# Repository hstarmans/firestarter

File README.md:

# Hexastorm PCB

KiCad design files for **Hexastorm**, an open-hardware laser direct imager (LDI). An ESP32-S3 handles communication and motion control, while an iCE40 UP5K FPGA generates synchronized laser pulses for the rotating polygon prism.

The design files are organized into two parts:

## 1. Laser Module

PCBs forming the scanhead assembly (see [hexastorm_design](https://github.com/hstarmans/hexastorm_design) for complete CAD):

* **Prism Drive:** PCBs to spin the optical prism using either an external BLDC motor or an experimental PCB stator motor.
* **Laser Control:** Diode driver and photodiode sync circuit.
* **Maxwell Dock:** Receiver PCB with kinematic ball mounts and magnet sockets.

## 2. Base Board

Single-board controller for 3-axis motion and laser timing. Intended for desktop CNC frames (such as the CNC 3018 Pro, for which it is a drop-in replacement):

* **MCU:** ESP32-S3 (N32R8V) with 8MB Octal PSRAM for line buffers.
* **FPGA:** Lattice iCE40 UP5K for laser pulse timing synced to the prism photodiode index.
* **Camera:** 24-pin FPC connector for an OV2640 camera module.
* **Motion:** Sockets for 3x stepper drivers (TMC2209) for X, Y, and Z axes.
* **Laser:** Header for one laser scanhead.
* **Power:** 24V input with onboard 12V buck regulator for the laser module and cooling fan.
* **USB:** USB-C for data and flashing.

---

# Resources & Links

* **Blog & Build Logs:** [Hackaday.io project](https://hackaday.io/project/21933-open-hardware-fast-high-resolution-laser)
* **BOM & Costing:** Generated with [KiCost](https://github.com/hildogjr/KiCost) (see [developer.md](developer.md))
* **CAD Files:** [hexastorm_design](https://github.com/hstarmans/hexastorm_design)
* **Optical Simulation:** [opticaldesign](https://github.com/hstarmans/opticaldesign)

# Status

* **Exposure Verification:** High-resolution optical scanning and exposure have been validated in hardware (see [demonstration video](https://youtu.be/dR09Tev0cPk)).
* **Base Board:** Fabricated, tested, and verified functional (ESP32-S3, iCE40 UP5K FPGA, stepper drivers, and power regulation).
* **Laser Module:** Scanhead structure, optics, diode driver, and kinematic docking are verified. The integrated PCB stator motor concept is proven, though the latest stator board revision has not yet been tested.

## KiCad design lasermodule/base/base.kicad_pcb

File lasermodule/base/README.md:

# Scanhead Base Plate

Structural bottom floor of the laser scanhead module. Hosts mounting holes for the prism motor assembly, internal optics brackets, and kinematic docking interfaces.
A female pinheader is shown but this one is normally not placed.

## Key Details

* **Role:** Bottom structural plate of scanhead housing
* **Material:** 1.6mm FR4 PCB material
* **Features:** Prism spindle mounting, beam pass-through cutouts, interlocking tabs

---

*Part of the [Hexastorm (Firestarter)](../../README.md) open-hardware laser direct imaging project.*

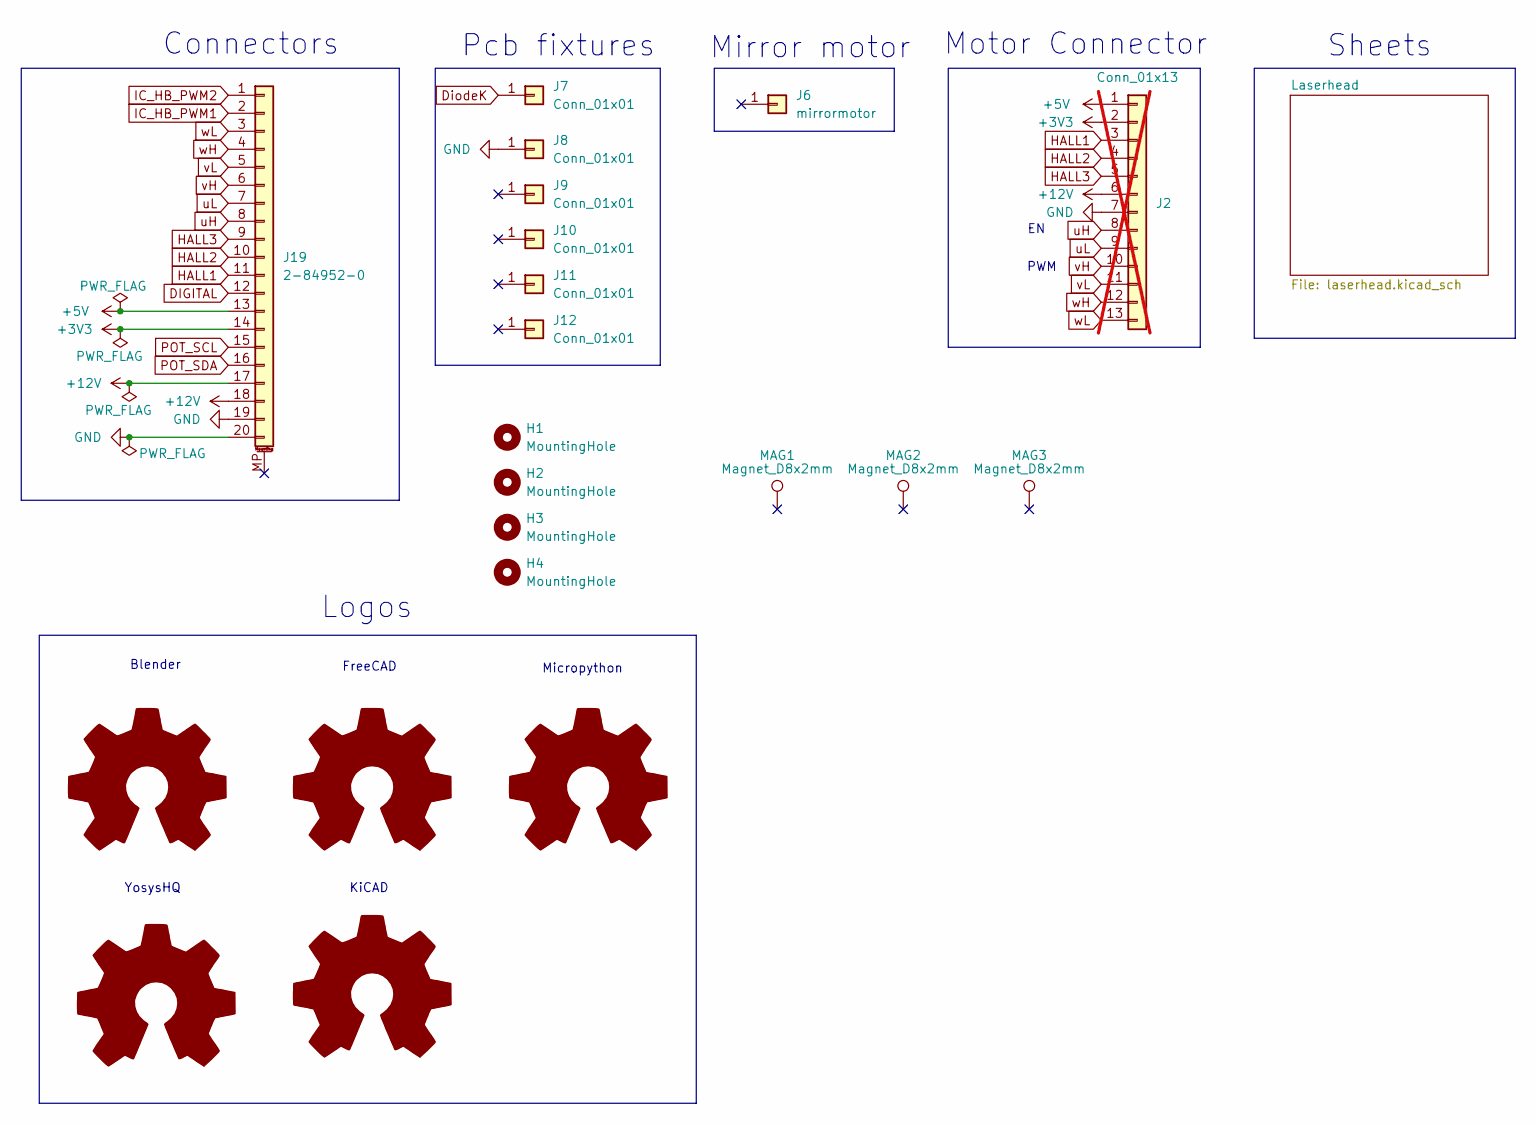
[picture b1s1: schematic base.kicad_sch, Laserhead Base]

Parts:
H1, H2, H3, H4: MountingHole; MountingHole_2.2mm_M2; mouser# 710-970050244
J2: Conn_01x13; PinSocket_1x13_P2.00mm_Vertical; not fitted
J6: mirrormotor; mirror_motor
J7, J8, J9, J10, J11, J12: Conn_01x01; throughholeplate
J19: 2-84952-0; mouser# 571-2-84952-0
L1: Logo_Open_Hardware_Large; blender
L2: Logo_Open_Hardware_Large; yosys
L3: Logo_Open_Hardware_Large; kicad
L4: Logo_Open_Hardware_Large; freecad
L5: Logo_Open_Hardware_Large; micropython
MAG1, MAG2, MAG3: Magnet_D8x2mm; TestPoint_Pad_D8.0mm

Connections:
+3V3: J2.2, J19.14
+5V: J2.1, J19.13; also elsewhere on the board
+12V: J2.6, J19.17, J19.18; also elsewhere on the board
DIGITAL: J19.12; also elsewhere on the board
DiodeK: J7.1 (Pin_1_1); also elsewhere on the board
GND: J2.7, J8.1 (Pin_1_1), J19.19, J19.20; also elsewhere on the board
HALL1: J2.3, J19.11
HALL2: J2.4, J19.10
HALL3: J2.5, J19.9
IC_HB_PWM1: J19.2; also elsewhere on the board
IC_HB_PWM2: J19.1; also elsewhere on the board
POT_SCL: J19.15; also elsewhere on the board
POT_SDA: J19.16; also elsewhere on the board
uH: J2.8, J19.8
uL: J2.9, J19.7
vH: J2.10, J19.6
vL: J2.11, J19.5
wH: J2.12, J19.4
wL: J2.13, J19.3

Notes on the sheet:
PWM
Micropython
YosysHQ
FreeCAD
Logos
KiCAD
Motor Connector
Blender
Connectors
Sheets
Mirror motor
Pcb fixtures

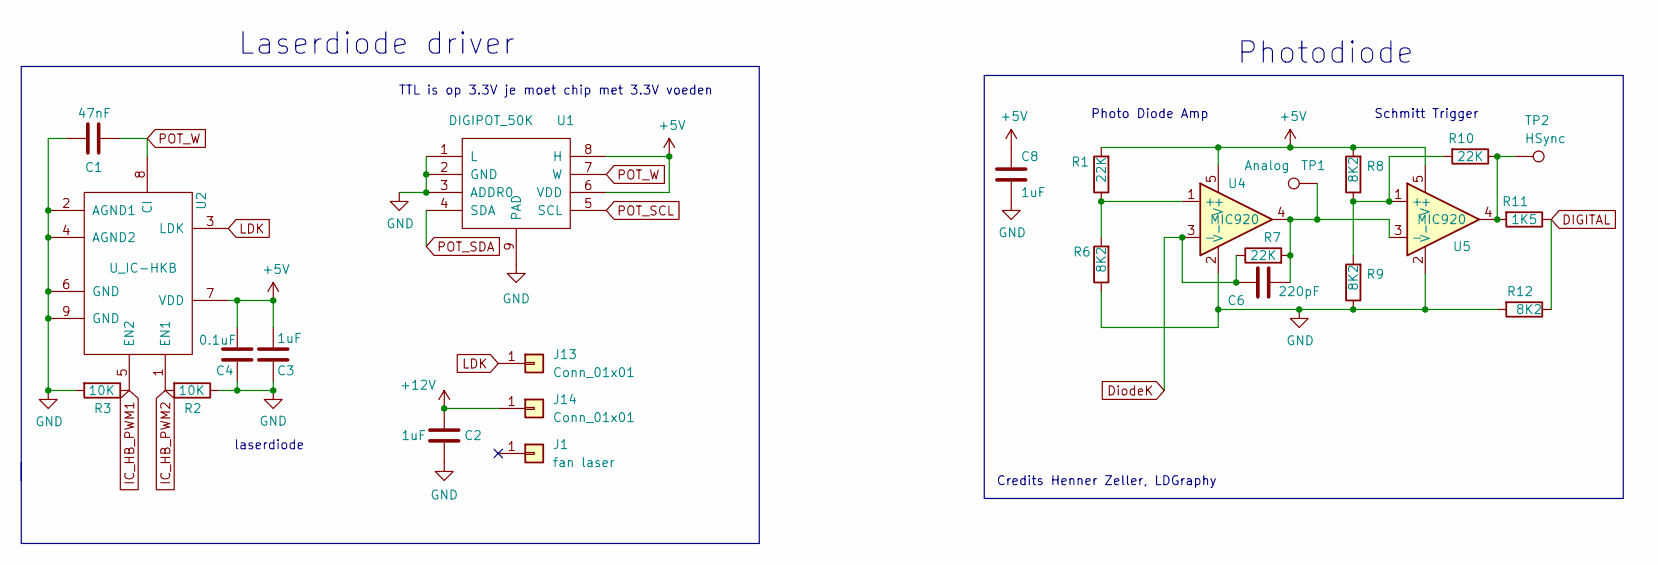
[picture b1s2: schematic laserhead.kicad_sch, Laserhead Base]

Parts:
C1: 47nF; C_0805_2012Metric_Pad1.18x1.45mm_HandSolder; mouser# 77-VJ0805Y473JXXCBC
C2, C8: 1uF; C_0805_2012Metric_Pad1.18x1.45mm_HandSolder; mouser# 581-08055C105KAT2A; farnell# 2094043
C3: 1uF; C_0805_2012Metric_Pad1.18x1.45mm_HandSolder; mouser# 581-08055C105KAT2A
C4: 0.1uF; C_0805_2012Metric_Pad1.18x1.45mm_HandSolder; mouser# 80-C0805C104J5R; farnell# 1414663
C6: 220pF; C_0805_2012Metric_Pad1.18x1.45mm_HandSolder; mouser# 80-C0805C221J5GAUTO
J1: fan laser; mouser# 490-HSB01-080808
J13, J14: Conn_01x01; throughholeplate
R1, R7, R10: 22K; R_0805_2012Metric_Pad1.20x1.40mm_HandSolder; mouser# 594-MCU08050C2202FP5
R2, R3: 10K; R_0805_2012Metric_Pad1.20x1.40mm_HandSolder; mouser# 71-CRCW080510K0JNEAC; farnell# 2826162
R6, R8, R9, R12: 8K2; R_0805_2012Metric_Pad1.20x1.40mm_HandSolder; mouser# 652-CR0805FX-8251ELF
R11: 1K5; R_0805_2012Metric_Pad1.20x1.40mm_HandSolder; mouser# 652-CR0805JW-152ELF
TP1: Analog; TestPoint_Pad_D1.0mm
TP2: HSync; TestPoint_Pad_D1.0mm
U1: DIGIPOT_50K; TDFN-8-1EP; mouser# 700-MAX5395MATA+T
U2: U_IC-HKB; ICHKB
U4: MIC920; SOT-353_SC-70-5; mouser# 998-MIC920YC5TR
U5: MIC920; SOT-353_SC-70-5; mouser# 998-MIC920YC5TR; farnell# 2920854

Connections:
+5V: C3.2, C4.2, C8.1, R1.2, R8.2, U1.6 (VDD), U1.8 (H), U2.7 (VDD), U4.5 (V+), U5.5 (V+); also elsewhere on the board
+12V: C2.2, J14.1 (Pin_1_1); also elsewhere on the board
DIGITAL: R11.1, R12.1; also elsewhere on the board
DiodeK: C6.2, R7.1, U4.3 (-); also elsewhere on the board
GND: C1.1, C2.1, C3.1, C4.1, C8.2, R2.1, R3.2, R6.1, R9.1, R12.2, U1.1 (L), U1.2 (GND), U1.3 (ADDR0), U1.9 (PAD), U2.2 (AGND1), U2.4 (AGND2), U2.6 (GND), U2.9 (GND), U4.2 (V-), U5.2 (V-); also elsewhere on the board
IC_HB_PWM1: R3.1, U2.5 (EN2); also elsewhere on the board
IC_HB_PWM2: R2.2, U2.1 (EN1); also elsewhere on the board
LDK: J13.1 (Pin_1_1), U2.3 (LDK)
unnamed: R10.1, R11.2, TP2.1 (1_1), U5.4
unnamed: R1.1, R6.2, U4.1 (+)
unnamed: R8.1, R9.2, R10.2, U5.1 (+)
unnamed: C6.1, R7.2, TP1.1 (1_1), U4.4, U5.3 (-)
POT_SCL: U1.5 (SCL); also elsewhere on the board
POT_SDA: U1.4 (SDA); also elsewhere on the board
POT_W: C1.2, U1.7 (W), U2.8 (CI)

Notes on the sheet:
Photo Diode Amp
TTL is op 3.3V je moet chip met 3.3V voeden
Laserdiode driver
Schmitt Trigger
Credits Henner Zeller, LDGraphy
laserdiode
Photodiode

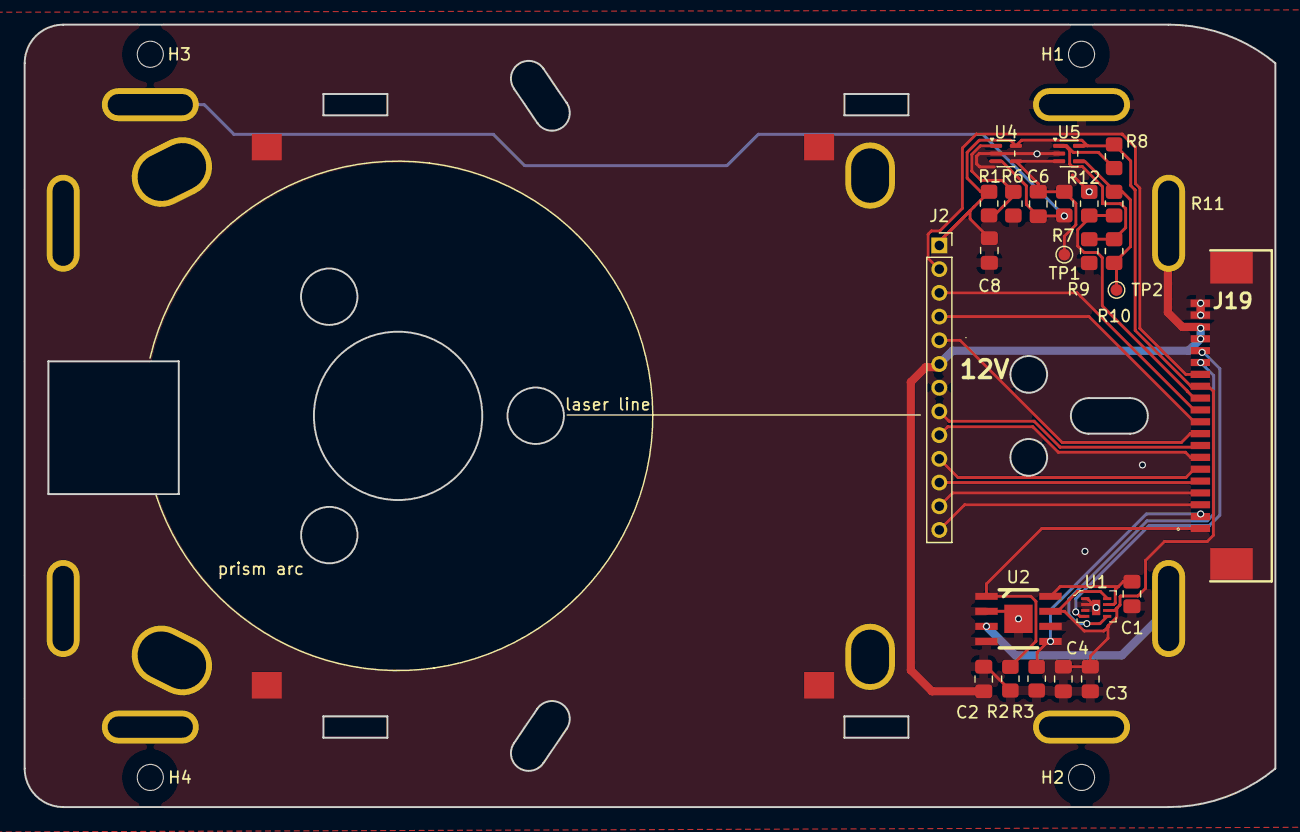
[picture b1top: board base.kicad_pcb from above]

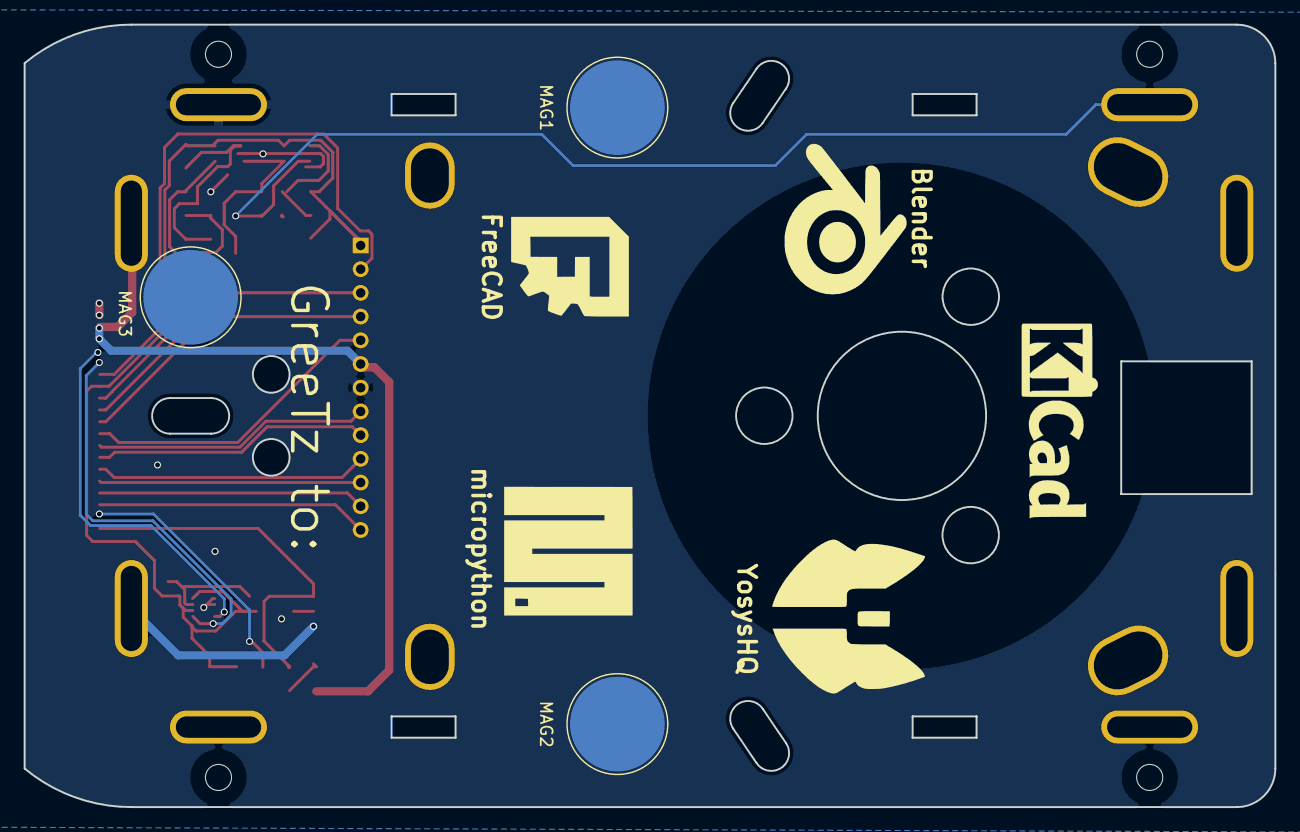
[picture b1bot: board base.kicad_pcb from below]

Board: 2 copper layers, 105.5 x 66.0 mm, 45 parts (8 on the bottom side), 25 nets.

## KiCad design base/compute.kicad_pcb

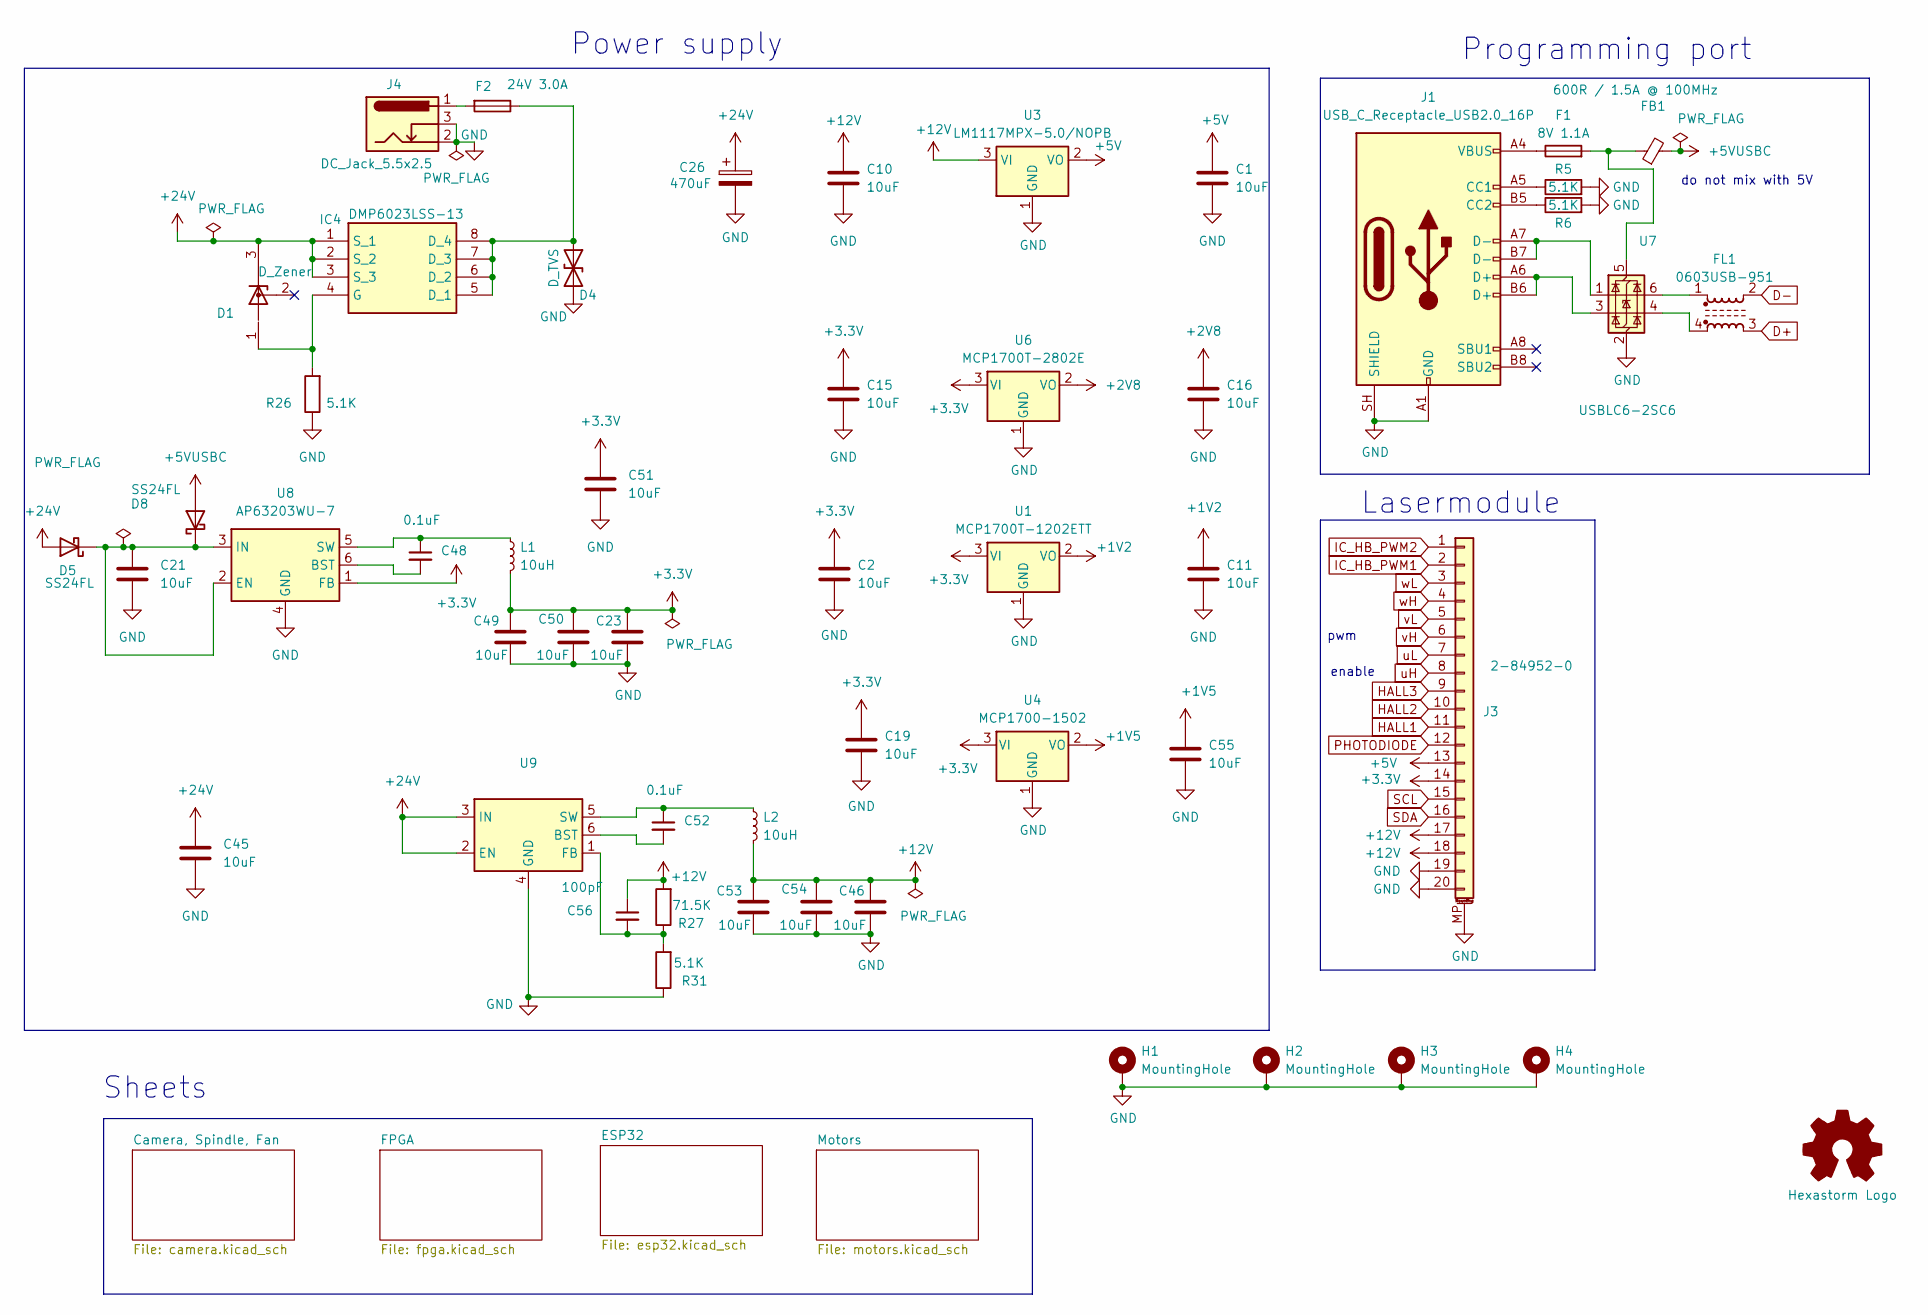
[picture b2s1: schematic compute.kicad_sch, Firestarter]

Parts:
C1, C2, C10, C11, C15, C16, C19, C49, C50, C53, C54, C55: 10uF; C_0805_2012Metric_Pad1.18x1.45mm_HandSolder; mouser# 81-GRM21BR61H106KE3L; farnell# 3790440
C21, C23, C45, C46, C51: 10uF; C_0805_2012Metric_Pad1.18x1.45mm_HandSolder; mouser# 81-GRM21BR61H106KE3L
C26: 470uF; CP_Elec_10x10.5; mouser# 667-EEE-FK1V471SP; farnell# 2507737
C48, C52: 0.1uF; C_0805_2012Metric_Pad1.18x1.45mm_HandSolder; mouser# 80-C0805C104J5R
C56: 100pF; C_0805_2012Metric_Pad1.18x1.45mm_HandSolder; mouser# 603-CC805JRNPO9BN101
D1: D_Zener; SOT-23; mouser# 863-BZX84C12LT1G
D4: D_TVS; D_SMB; mouser# 652-SMBJ26CA; farnell# 1827683
D5, D8: SS24FL; D_SMA; mouser# 512-SS24FL; farnell# 2822566
F1: 8V 1.1A; Fuse_1206_3216Metric; mouser# 576-1206L110THYR; farnell# 2383294
F2: 24V 3.0A; Fuse_2920_7451Metric; mouser# 652-MF-LSMF300/24X-2
FB1: 600R / 1.5A @ 100MHz; L_0805_2012Metric; mouser# 81-BLM21PG601SN1D
FL1: 0603USB-951; L_CommonModeChoke_Coilcraft_0603USB; mouser# 994-0603USB-142MLC
G1: hexastorm
H1, H2, H3, H4: MountingHole; MountingHole_2.5mm_Pad_Via; mouser# 710-970050244
IC4: DMP6023LSS-13; SOIC-8_3.9x4.9mm_P1.27mm; Manufacturer_Part_Number DMP6023LSS-13; Mouser Part Number 621-DMP6023LSS-13
J1: USB_C_Receptacle_USB2.0_16P; USB_C_Receptacle_GCT_USB4105-xx-A_16P_TopMnt_Horizontal; mouser# 640-USB4105-GF-A
J3: 2-84952-0; mouser# 571-2-84952-0
J4: DC_Jack_5.5x2.5; BarrelJack_CUI_PJ-079BH_Horizontal; mouser# 490-PJ-079BH
L1, L2: 10uH; L_Bourns_SRP5030T; mouser# 810-SPM5030T-100M-HZ
R5, R6, R26, R31: 5.1K; R_0805_2012Metric; mouser# -71-CRCW0805-5.1K-E3; farnell# 1469937
R27: 71.5K; R_0805_2012Metric; mouser# 603-RC0805FR-0771K5L; farnell# 3952038
U1: MCP1700T-1202ETT; SOT-23; mouser# 579-MCP1700T1202E/TT
U3: LM1117MPX-5.0/NOPB; SOT-223-3_TabPin2; mouser# 926-LM1117MPX5.0NOPB; farnell# 3007506
U4: MCP1700-1502; SOT-23; mouser# 579-MCP1700T1502E/TT
U6: MCP1700T-2802E; SOT-23; mouser# 579-MCP1700T-2802ETT
U7: USBLC6-2SC6; SOT-23-6; mouser# 511-USBLC6-2SC6; farnell# 1269406
U8: AP63203WU-7; TSOT-23-6; mouser# 621-AP63203WU-7; farnell# 3518307
U9: TSOT-23-6; mouser# 621-AP63200WU-7; farnell# 3518305

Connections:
+1V2: C11.1, U1.2 (VO); also elsewhere on the board
+1V5: C55.1, U4.2 (VO); also elsewhere on the board
+2V8: C16.1, U6.2 (VO); also elsewhere on the board
+3.3V: C2.1, C15.1, C19.1, C23.1, C49.1, C50.1, C51.1, J3.14, L1.2, U1.3 (VI), U4.3 (VI), U6.3 (VI), U8.1 (FB); also elsewhere on the board
+5V: C1.1, J3.13, U3.2 (VO)
+5VUSBC: D8.2 (A), FB1.2
+12V: C10.1, C46.1, C53.1, C54.1, C56.1, J3.17, J3.18, L2.2, R27.2, U3.3 (VI); also elsewhere on the board
+24V: C26.1, C45.1, D1.3 (K), D5.2 (A), IC4.1 (S_1), IC4.2 (S_2), IC4.3 (S_3), U9.2 (EN), U9.3 (IN); also elsewhere on the board
D+: FL1.3; also elsewhere on the board
D-: FL1.2; also elsewhere on the board
GND: C1.2, C2.2, C10.2, C11.2, C15.2, C16.2, C19.2, C21.2, C23.2, C26.2, C45.2, C46.2, C49.2, C50.2, C51.2, C53.2, C54.2, C55.2, D4.2 (A2), H1.1 (1_1), H2.1 (1_1), H3.1 (1_1), H4.1 (1_1), J1.A1 (GND), J1.A12 (GND), J1.B1 (GND), J1.B12 (GND), J1.SH (SHIELD), J3.19, J3.20, J3.MP (MountPin), J4.2, J4.3, R5.2, R6.2, R26.1, R31.1, U1.1 (GND), U3.1 (GND), U4.1 (GND), U6.1 (GND), U7.2 (GND), U8.4 (GND), U9.4 (GND); also elsewhere on the board
HALL1: J3.11; also elsewhere on the board
HALL2: J3.10; also elsewhere on the board
HALL3: J3.9; also elsewhere on the board
IC_HB_PWM1: J3.2; also elsewhere on the board
IC_HB_PWM2: J3.1; also elsewhere on the board
unnamed: D4.1 (A1), F2.1, IC4.5 (D_1), IC4.6 (D_2), IC4.7 (D_3), IC4.8 (D_4)
unnamed: C21.1, D5.1 (K), D8.1 (K), U8.2 (EN), U8.3 (IN)
unnamed: F1.1, J1.A4 (VBUS), J1.A9 (VBUS), J1.B4 (VBUS), J1.B9 (VBUS)
unnamed: F2.2, J4.1
unnamed: FL1.1, U7.6 (I/O1)
unnamed: FL1.4, U7.4 (I/O2)
unnamed: D1.1 (K), IC4.4 (G), R26.2
unnamed: J1.A5 (CC1), R5.1
unnamed: J1.B5 (CC2), R6.1
unnamed: J1.A6 (D+), J1.B6 (D+), U7.3 (I/O2)
unnamed: J1.A7 (D-), J1.B7 (D-), U7.1 (I/O1)
unnamed: F1.2, FB1.1, U7.5 (VBUS)
unnamed: C48.2, U8.6 (BST)
unnamed: C48.1, L1.1, U8.5 (SW)
unnamed: C52.2, U9.6 (BST)
unnamed: C56.2, R27.1, R31.2, U9.1 (FB)
unnamed: C52.1, L2.1, U9.5 (SW)
PHOTODIODE: J3.12; also elsewhere on the board
SCL: J3.15; also elsewhere on the board
SDA: J3.16; also elsewhere on the board
uH: J3.8; also elsewhere on the board
uL: J3.7; also elsewhere on the board
vH: J3.6; also elsewhere on the board
vL: J3.5; also elsewhere on the board
wH: J3.4; also elsewhere on the board
wL: J3.3; also elsewhere on the board

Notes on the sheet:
pwm
Programming port
Sheets
Power supply
enable
Lasermodule
do not mix with 5V

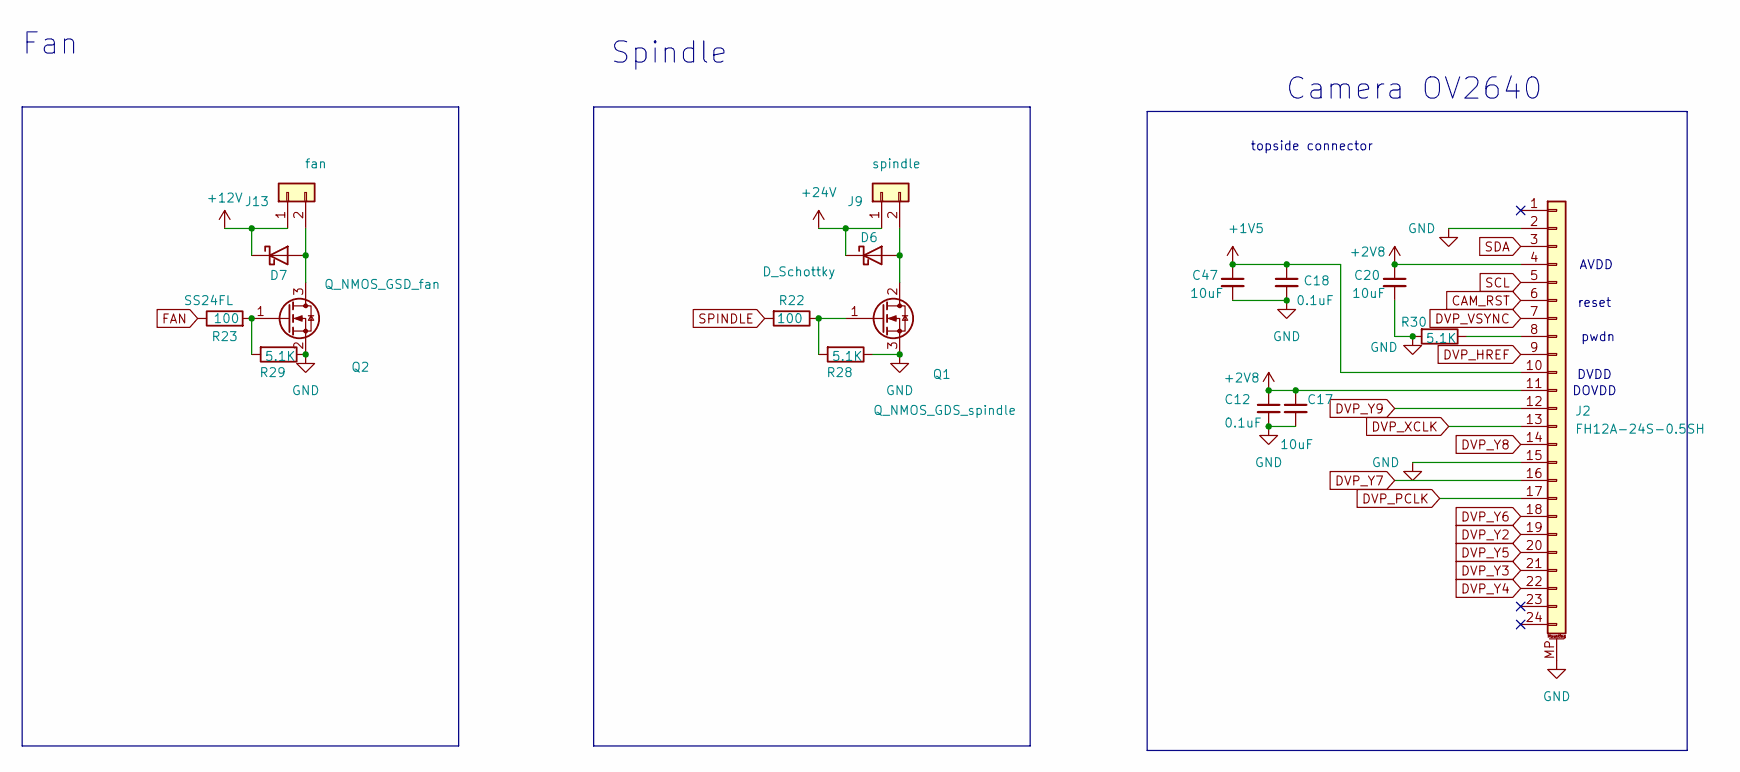
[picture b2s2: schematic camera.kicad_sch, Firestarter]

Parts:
C12, C18: 0.1uF; C_0805_2012Metric_Pad1.18x1.45mm_HandSolder; mouser# 80-C0805C104J5R
C17, C20, C47: 10uF; C_0805_2012Metric_Pad1.18x1.45mm_HandSolder; mouser# 81-GRM21BR61H106KE3L; farnell# 3790440
D6: D_Schottky; D_SMA; mouser# 750-SS56-HF
D7: SS24FL; D_SMA; mouser# 512-SS24FL; farnell# 2822566
J2: FH12A-24S-0.5SH; Hirose_FH12-24S-0.5SH_1x24-1MP_P0.50mm_Horizontal; mouser# 798-FH12A-24S0.5SH55; farnell# 1324565
J9: spindle; JST_VH_B2P-VH_1x02_P3.96mm_Vertical; mouser# 306-B2PVHBKLFSN
J13: fan; JST_B2B-XH-A_LF__SN_; mouser# 306-B2BXHALFSNP
Q1: Q_NMOS_GDS_spindle; TO-252-2; mouser# 512-FDD8447L
Q2: Q_NMOS_GSD_fan; SOT-23; mouser# 512-2N7002
R22, R23: 100; R_0805_2012Metric; mouser# 71-CRCW0805-100
R28, R29, R30: 5.1K; R_0805_2012Metric; mouser# -71-CRCW0805-5.1K-E3; farnell# 1469937

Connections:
+1V5: C18.1, C47.1, J2.10; also elsewhere on the board
+2V8: C12.1, C17.1, C20.1, J2.4, J2.11; also elsewhere on the board
+12V: D7.1 (K), J13.1; also elsewhere on the board
+24V: D6.1 (K), J9.1; also elsewhere on the board
CAM_RST: J2.6; also elsewhere on the board
DVP_HREF: J2.9; also elsewhere on the board
DVP_PCLK: J2.17; also elsewhere on the board
DVP_VSYNC: J2.7; also elsewhere on the board
DVP_XCLK: J2.13; also elsewhere on the board
DVP_Y2: J2.19; also elsewhere on the board
DVP_Y3: J2.21; also elsewhere on the board
DVP_Y4: J2.22; also elsewhere on the board
DVP_Y5: J2.20; also elsewhere on the board
DVP_Y6: J2.18; also elsewhere on the board
DVP_Y7: J2.16; also elsewhere on the board
DVP_Y8: J2.14; also elsewhere on the board
DVP_Y9: J2.12; also elsewhere on the board
FAN: R23.1; also elsewhere on the board
GND: C12.2, C17.2, C18.2, C20.2, C47.2, J2.2, J2.15, J2.MP (MountPin), Q1.3 (S), Q2.2 (S), R28.1, R29.1, R30.2; also elsewhere on the board
unnamed: D6.2 (A), J9.2, Q1.2 (D)
unnamed: D7.2 (A), J13.2, Q2.3 (D)
unnamed: J2.8, R30.1
unnamed: Q1.1 (G), R22.1, R28.2
unnamed: Q2.1 (G), R23.2, R29.2
SCL: J2.5; also elsewhere on the board
SDA: J2.3; also elsewhere on the board
SPINDLE: R22.2; also elsewhere on the board

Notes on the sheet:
DOVDD
DVDD
Spindle
pwdn
topside connector
reset
Fan
Camera OV2640
AVDD

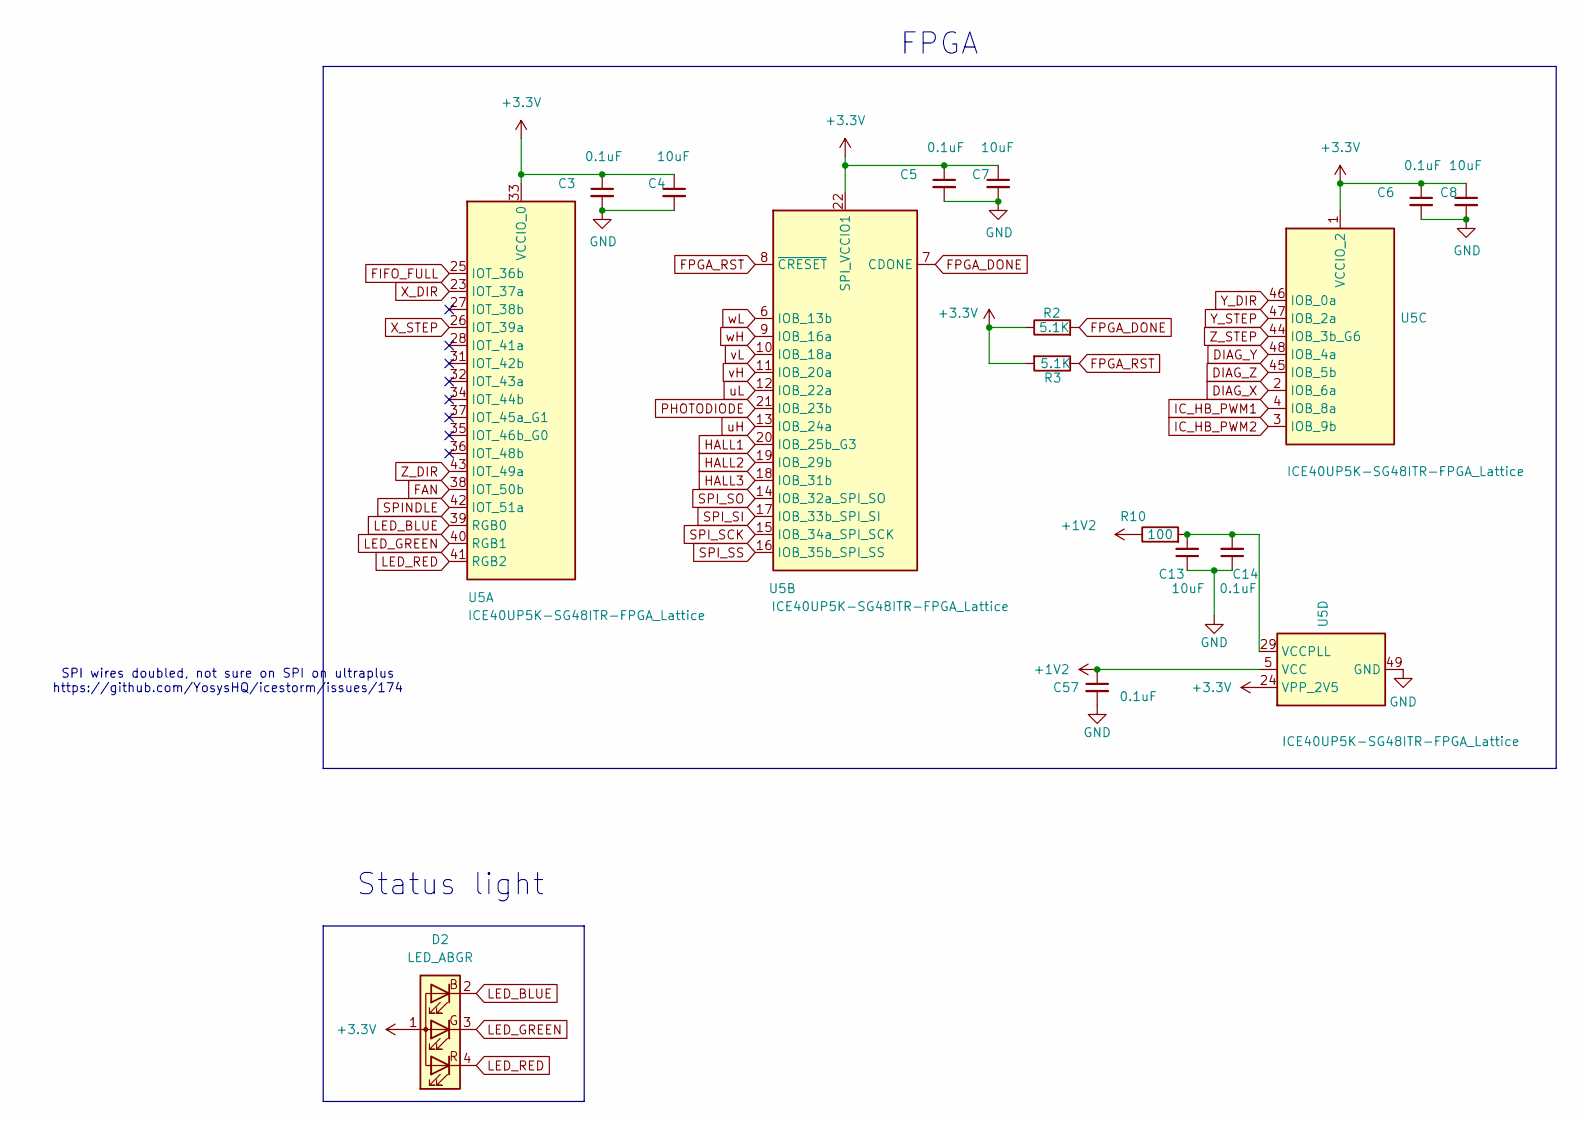
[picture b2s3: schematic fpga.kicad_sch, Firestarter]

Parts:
C3, C5, C6, C14, C57: 0.1uF; C_0805_2012Metric_Pad1.18x1.45mm_HandSolder; mouser# 80-C0805C104J5R
C4, C7, C8, C13: 10uF; C_0805_2012Metric_Pad1.18x1.45mm_HandSolder; mouser# 81-GRM21BR61H106KE3L; farnell# 3790440
D2: LED_ABGR; LED_Cree-PLCC4_2x2mm_CW; mouser# 941-CLMVCFKACL1D1L71; farnell# 3625420
R2, R3: 5.1K; R_0805_2012Metric; mouser# -71-CRCW0805-5.1K-E3; farnell# 1469937
R10: 100; R_0805_2012Metric; mouser# 71-CRCW0805-100
U5: ICE40UP5K-SG48ITR-FPGA_Lattice; QFN-48-1EP_7x7mm_P0.5mm_EP5.6x5.6mm; mouser# 842-ICE40UP5K-SG48I

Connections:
+1V2: C57.1, R10.1, U5.5 (VCC), U5.30 (VCC); also elsewhere on the board
+3.3V: C3.1, C4.1, C5.1, C6.1, C7.1, C8.1, D2.1 (A), R2.1, R3.2, U5.1 (VCCIO_2), U5.22 (SPI_VCCIO1), U5.24 (VPP_2V5), U5.33 (VCCIO_0); also elsewhere on the board
DIAG_X: U5.2 (IOB_6a); also elsewhere on the board
DIAG_Y: U5.48 (IOB_4a); also elsewhere on the board
DIAG_Z: U5.45 (IOB_5b); also elsewhere on the board
FAN: U5.38 (IOT_50b); also elsewhere on the board
FIFO_FULL: U5.25 (IOT_36b); also elsewhere on the board
FPGA_DONE: R2.2, U5.7 (CDONE); also elsewhere on the board
FPGA_RST: R3.1, U5.8 (~CRESET); also elsewhere on the board
GND: C3.2, C4.2, C5.2, C6.2, C7.2, C8.2, C13.1, C14.1, C57.2, U5.49 (GND); also elsewhere on the board
HALL1: U5.20 (IOB_25b_G3); also elsewhere on the board
HALL2: U5.19 (IOB_29b); also elsewhere on the board
HALL3: U5.18 (IOB_31b); also elsewhere on the board
IC_HB_PWM1: U5.4 (IOB_8a); also elsewhere on the board
IC_HB_PWM2: U5.3 (IOB_9b); also elsewhere on the board
LED_BLUE: D2.2 (BK), U5.39 (RGB0)
LED_GREEN: D2.3 (GK), U5.40 (RGB1)
LED_RED: D2.4 (RK), U5.41 (RGB2)
unnamed: C13.2, C14.2, R10.2, U5.29 (VCCPLL)
PHOTODIODE: U5.21 (IOB_23b); also elsewhere on the board
SPINDLE: U5.42 (IOT_51a); also elsewhere on the board
SPI_SCK: U5.15 (IOB_34a_SPI_SCK); also elsewhere on the board
SPI_SI: U5.17 (IOB_33b_SPI_SI); also elsewhere on the board
SPI_SO: U5.14 (IOB_32a_SPI_SO); also elsewhere on the board
SPI_SS: U5.16 (IOB_35b_SPI_SS); also elsewhere on the board
X_DIR: U5.23 (IOT_37a); also elsewhere on the board
X_STEP: U5.26 (IOT_39a); also elsewhere on the board
Y_DIR: U5.46 (IOB_0a); also elsewhere on the board
Y_STEP: U5.47 (IOB_2a); also elsewhere on the board
Z_DIR: U5.43 (IOT_49a); also elsewhere on the board
Z_STEP: U5.44 (IOB_3b_G6); also elsewhere on the board
uH: U5.13 (IOB_24a); also elsewhere on the board
uL: U5.12 (IOB_22a); also elsewhere on the board
vH: U5.11 (IOB_20a); also elsewhere on the board
vL: U5.10 (IOB_18a); also elsewhere on the board
wH: U5.9 (IOB_16a); also elsewhere on the board
wL: U5.6 (IOB_13b); also elsewhere on the board

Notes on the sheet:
FPGA
SPI wires doubled, not sure on SPI on ultraplus https://github.com/YosysHQ/icestorm/issues/174
Status light
